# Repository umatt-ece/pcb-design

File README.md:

# pcb-design
Schematics, documentation, and guidelines for all of our custom PCB projects.

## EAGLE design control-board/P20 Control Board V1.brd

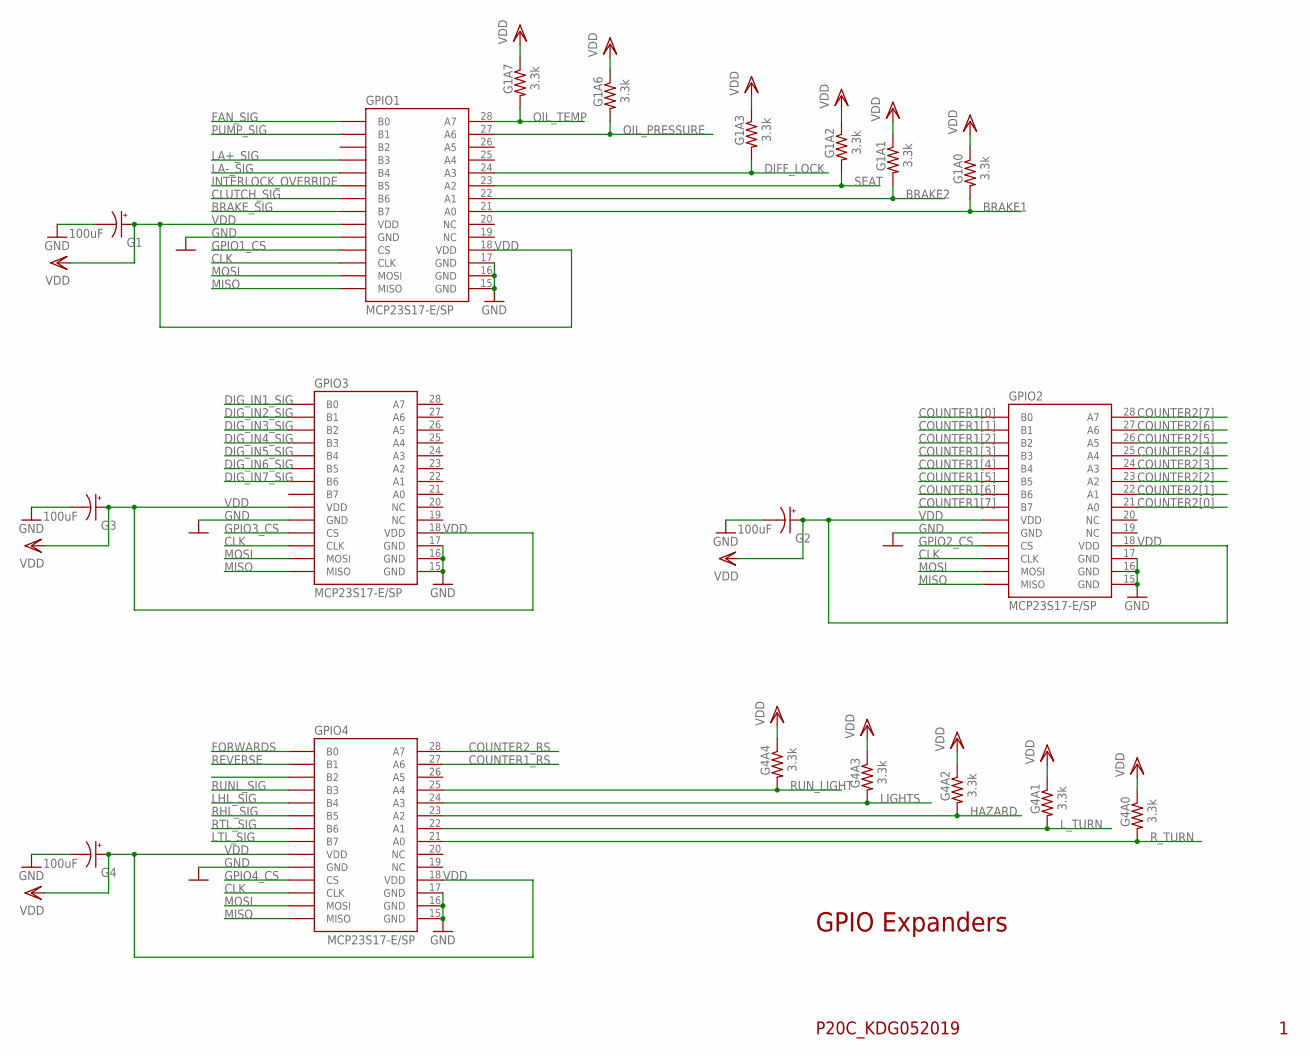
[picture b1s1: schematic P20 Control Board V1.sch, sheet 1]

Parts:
G1, G2, G3, G4: 100uF; TAP5-80
G1A0, G1A1, G1A2, G1A3, G1A6, G1A7, G4A0, G4A1, G4A2, G4A3, G4A4: 3.3k; 0207/10
GPIO1, GPIO2, GPIO3, GPIO4: MCP23S17-E/SP; GPIO_XPDR

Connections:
BRAKE1: G1A0.2, GPIO1.21 (A0); also elsewhere on the board
BRAKE2: G1A1.2, GPIO1.22 (A1); also elsewhere on the board
BRAKE_SIG: GPIO1.8 (B7); also elsewhere on the board
CLK: GPIO1.12 (CLK), GPIO2.12 (CLK), GPIO3.12 (CLK), GPIO4.12 (CLK); also elsewhere on the board
CLUTCH_SIG: GPIO1.7 (B6); also elsewhere on the board
COUNTER1[0]: GPIO2.1 (B0); also elsewhere on the board
COUNTER1[1]: GPIO2.2 (B1); also elsewhere on the board
COUNTER1[2]: GPIO2.3 (B2); also elsewhere on the board
COUNTER1[3]: GPIO2.4 (B3); also elsewhere on the board
COUNTER1[4]: GPIO2.5 (B4); also elsewhere on the board
COUNTER1[5]: GPIO2.6 (B5); also elsewhere on the board
COUNTER1[6]: GPIO2.7 (B6); also elsewhere on the board
COUNTER1[7]: GPIO2.8 (B7); also elsewhere on the board
COUNTER1_RS: GPIO4.27 (A6); also elsewhere on the board
COUNTER2[0]: GPIO2.21 (A0); also elsewhere on the board
COUNTER2[1]: GPIO2.22 (A1); also elsewhere on the board
COUNTER2[2]: GPIO2.23 (A2); also elsewhere on the board
COUNTER2[3]: GPIO2.24 (A3); also elsewhere on the board
COUNTER2[4]: GPIO2.25 (A4); also elsewhere on the board
COUNTER2[5]: GPIO2.26 (A5); also elsewhere on the board
COUNTER2[6]: GPIO2.27 (A6); also elsewhere on the board
COUNTER2[7]: GPIO2.28 (A7); also elsewhere on the board
COUNTER2_RS: GPIO4.28 (A7); also elsewhere on the board
DIFF_LOCK: G1A3.2, GPIO1.24 (A3); also elsewhere on the board
DIG_IN1_SIG: GPIO3.1 (B0); also elsewhere on the board
DIG_IN2_SIG: GPIO3.2 (B1); also elsewhere on the board
DIG_IN3_SIG: GPIO3.3 (B2); also elsewhere on the board
DIG_IN4_SIG: GPIO3.4 (B3); also elsewhere on the board
DIG_IN5_SIG: GPIO3.5 (B4); also elsewhere on the board
DIG_IN6_SIG: GPIO3.6 (B5); also elsewhere on the board
DIG_IN7_SIG: GPIO3.7 (B6); also elsewhere on the board
FAN_SIG: GPIO1.1 (B0); also elsewhere on the board
FORWARDS: GPIO4.1 (B0)
GND: G1.-, G2.-, G3.-, G4.-, GPIO1.10 (GND), GPIO1.15 (GND), GPIO1.16 (GND), GPIO1.17 (GND), GPIO2.10 (GND), GPIO2.15 (GND), GPIO2.16 (GND), GPIO2.17 (GND), GPIO3.10 (GND), GPIO3.15 (GND), GPIO3.16 (GND), GPIO3.17 (GND), GPIO4.10 (GND), GPIO4.15 (GND), GPIO4.16 (GND), GPIO4.17 (GND); also elsewhere on the board
GPIO1_CS: GPIO1.11 (CS); also elsewhere on the board
GPIO2_CS: GPIO2.11 (CS); also elsewhere on the board
GPIO3_CS: GPIO3.11 (CS); also elsewhere on the board
GPIO4_CS: GPIO4.11 (CS); also elsewhere on the board
HAZARD: G4A2.2, GPIO4.23 (A2); also elsewhere on the board
INTERLOCK_OVERRIDE: GPIO1.6 (B5); also elsewhere on the board
LA+_SIG: GPIO1.4 (B3); also elsewhere on the board
LA-_SIG: GPIO1.5 (B4); also elsewhere on the board
LHL_SIG: GPIO4.5 (B4); also elsewhere on the board
LIGHTS: G4A3.2, GPIO4.24 (A3); also elsewhere on the board
LTL_SIG: GPIO4.8 (B7); also elsewhere on the board
L_TURN: G4A1.2, GPIO4.22 (A1); also elsewhere on the board
MISO: GPIO1.14 (MISO), GPIO2.14 (MISO), GPIO3.14 (MISO), GPIO4.14 (MISO); also elsewhere on the board
MOSI: GPIO1.13 (MOSI), GPIO2.13 (MOSI), GPIO3.13 (MOSI), GPIO4.13 (MOSI); also elsewhere on the board
OIL_PRESSURE: G1A6.2, GPIO1.27 (A6); also elsewhere on the board
OIL_TEMP: G1A7.2, GPIO1.28 (A7); also elsewhere on the board
PUMP_SIG: GPIO1.2 (B1); also elsewhere on the board
REVERSE: GPIO4.2 (B1)
RHL_SIG: GPIO4.6 (B5); also elsewhere on the board
RTL_SIG: GPIO4.7 (B6); also elsewhere on the board
RUNL_SIG: GPIO4.4 (B3); also elsewhere on the board
RUN_LIGHT: G4A4.2, GPIO4.25 (A4); also elsewhere on the board
R_TURN: G4A0.2, GPIO4.21 (A0); also elsewhere on the board
SEAT: G1A2.2, GPIO1.23 (A2); also elsewhere on the board
VDD: G1.+, G1A0.1, G1A1.1, G1A2.1, G1A3.1, G1A6.1, G1A7.1, G2.+, G3.+, G4.+, G4A0.1, G4A1.1, G4A2.1, G4A3.1, G4A4.1, GPIO1.9 (VDD), GPIO1.18 (VDD), GPIO2.9 (VDD), GPIO2.18 (VDD), GPIO3.9 (VDD), GPIO3.18 (VDD), GPIO4.9 (VDD), GPIO4.18 (VDD); also elsewhere on the board

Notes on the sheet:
GPIO Expanders
P20C_KDG052019

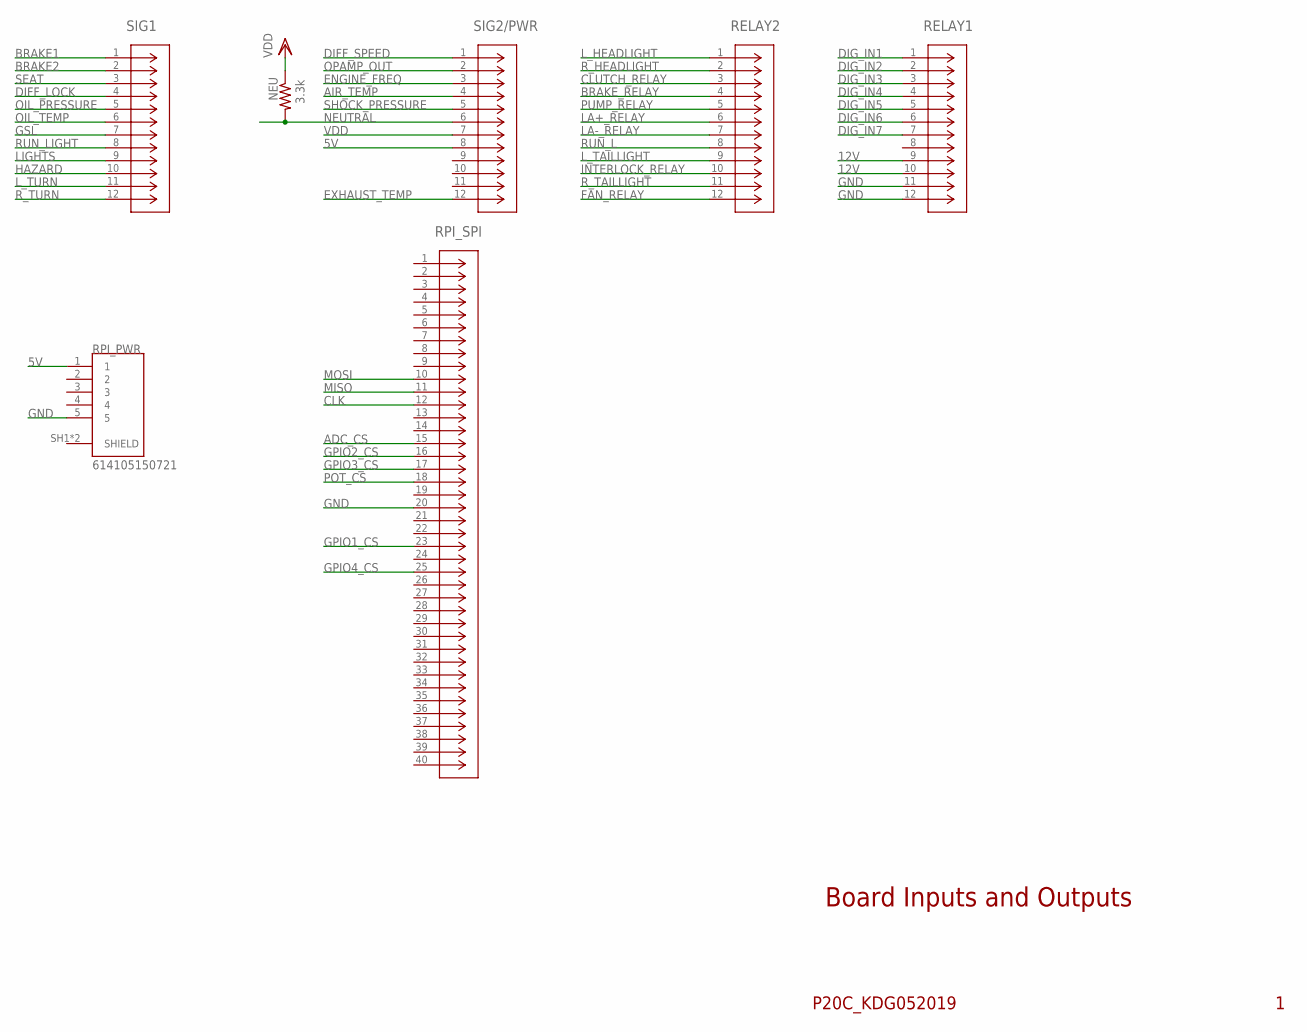
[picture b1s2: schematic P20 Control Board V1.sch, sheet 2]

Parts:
NEU: 3.3k; 0207/10
RELAY1, RELAY2: DTM13-12PA; CONN12_DTM13-12PA
RPI_PWR: 614105150721; WURTH_614105150721
RPI_SPI: 1-746610-9; CON40_P100X100-RIBBON
SIG1, SIG2/PWR: DTM13-12PA; CONN12_DTM13-12PA

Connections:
5V: RPI_PWR.1, SIG2/PWR.8; also elsewhere on the board
12V: RELAY1.9, RELAY1.10; also elsewhere on the board
ADC_CS: RPI_SPI.15; also elsewhere on the board
AIR_TEMP: SIG2/PWR.4; also elsewhere on the board
BRAKE1: SIG1.1; also elsewhere on the board
BRAKE2: SIG1.2; also elsewhere on the board
BRAKE_RELAY: RELAY2.4; also elsewhere on the board
CLK: RPI_SPI.12; also elsewhere on the board
CLUTCH_RELAY: RELAY2.3; also elsewhere on the board
DIFF_LOCK: SIG1.4; also elsewhere on the board
DIFF_SPEED: SIG2/PWR.1; also elsewhere on the board
DIG_IN1: RELAY1.1; also elsewhere on the board
DIG_IN2: RELAY1.2; also elsewhere on the board
DIG_IN3: RELAY1.3; also elsewhere on the board
DIG_IN4: RELAY1.4; also elsewhere on the board
DIG_IN5: RELAY1.5; also elsewhere on the board
DIG_IN6: RELAY1.6; also elsewhere on the board
DIG_IN7: RELAY1.7; also elsewhere on the board
ENGINE_FREQ: SIG2/PWR.3; also elsewhere on the board
EXHAUST_TEMP: SIG2/PWR.12; also elsewhere on the board
FAN_RELAY: RELAY2.12; also elsewhere on the board
GND: RELAY1.11, RELAY1.12, RPI_PWR.5, RPI_SPI.20; also elsewhere on the board
GPIO1_CS: RPI_SPI.23; also elsewhere on the board
GPIO2_CS: RPI_SPI.16; also elsewhere on the board
GPIO3_CS: RPI_SPI.17; also elsewhere on the board
GPIO4_CS: RPI_SPI.25; also elsewhere on the board
GSL: SIG1.7; also elsewhere on the board
HAZARD: SIG1.10; also elsewhere on the board
INTERLOCK_RELAY: RELAY2.10; also elsewhere on the board
LA+_RELAY: RELAY2.6; also elsewhere on the board
LA-_RELAY: RELAY2.7; also elsewhere on the board
LIGHTS: SIG1.9; also elsewhere on the board
L_HEADLIGHT: RELAY2.1; also elsewhere on the board
L_TAILLIGHT: RELAY2.9; also elsewhere on the board
L_TURN: SIG1.11; also elsewhere on the board
MISO: RPI_SPI.11; also elsewhere on the board
MOSI: RPI_SPI.10; also elsewhere on the board
NEUTRAL: NEU.2, SIG2/PWR.6; also elsewhere on the board
OIL_PRESSURE: SIG1.5; also elsewhere on the board
OIL_TEMP: SIG1.6; also elsewhere on the board
OPAMP_OUT: SIG2/PWR.2; also elsewhere on the board
POT_CS: RPI_SPI.18; also elsewhere on the board
PUMP_RELAY: RELAY2.5; also elsewhere on the board
RUN_L: RELAY2.8; also elsewhere on the board
RUN_LIGHT: SIG1.8; also elsewhere on the board
R_HEADLIGHT: RELAY2.2; also elsewhere on the board
R_TAILLIGHT: RELAY2.11; also elsewhere on the board
R_TURN: SIG1.12; also elsewhere on the board
SEAT: SIG1.3; also elsewhere on the board
SHOCK_PRESSURE: SIG2/PWR.5; also elsewhere on the board
VDD: NEU.1, SIG2/PWR.7; also elsewhere on the board

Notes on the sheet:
Board Inputs and Outputs
P20C_KDG052019

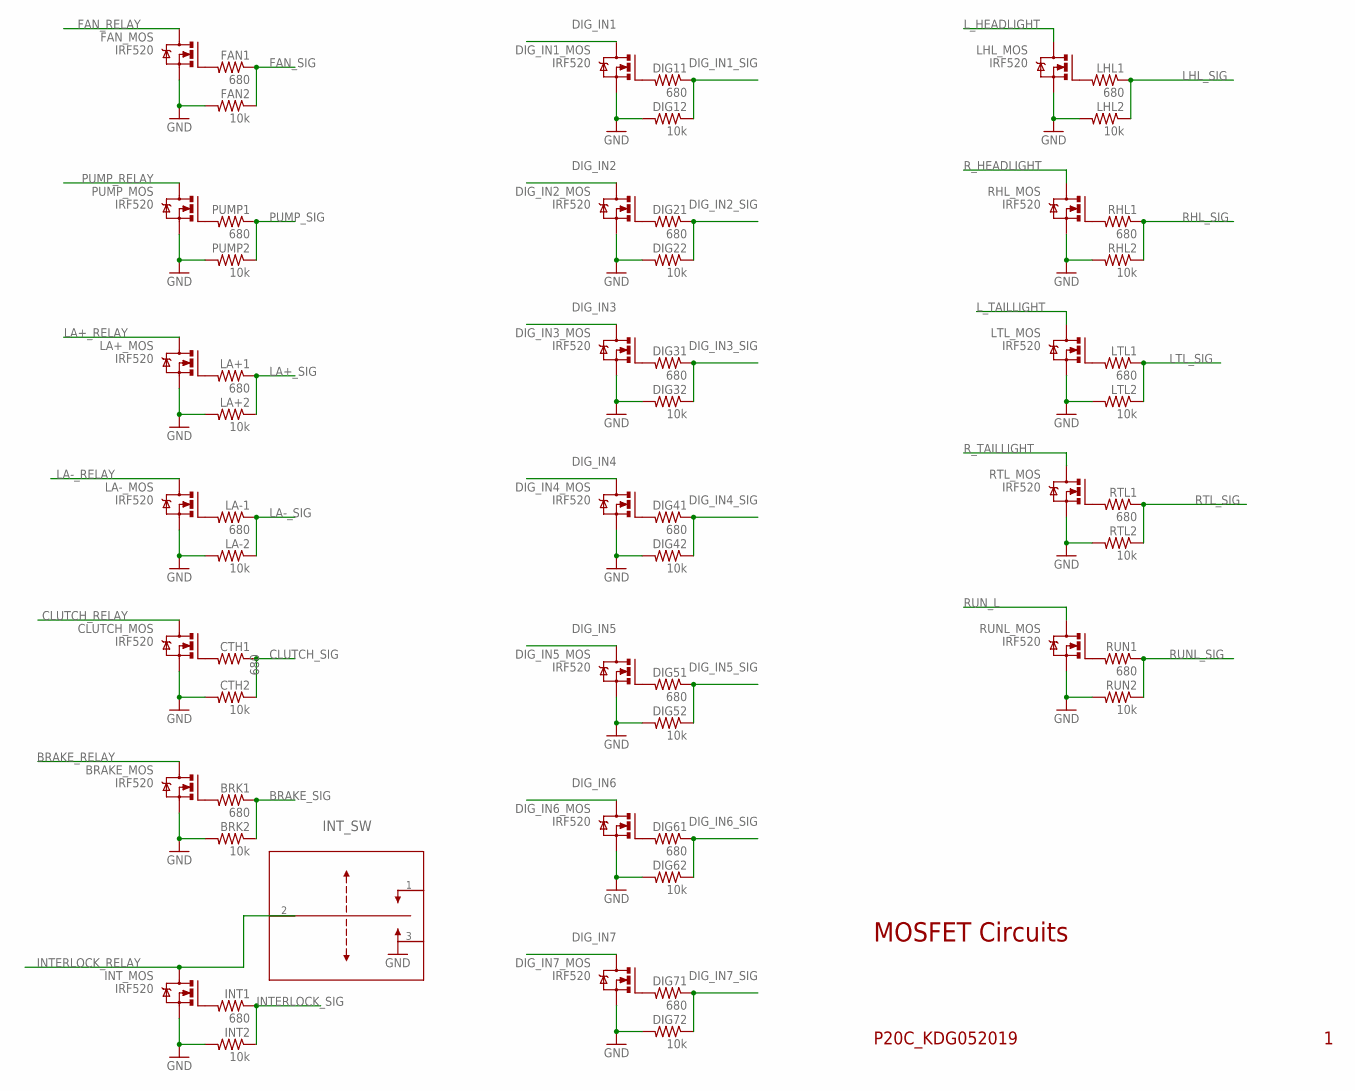
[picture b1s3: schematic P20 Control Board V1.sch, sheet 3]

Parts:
BRAKE_MOS: IRF520; TO220BV
BRK1: 680; 0207/10
BRK2: 10k; 0207/10
CLUTCH_MOS: IRF520; TO220BV
CTH1: 680; 0207/10
CTH2: 10k; 0207/10
DIG11, DIG21, DIG31, DIG41, DIG51, DIG61, DIG71: 680; 0207/10
DIG12, DIG22, DIG32, DIG42, DIG52, DIG62, DIG72: 10k; 0207/10
DIG_IN1_MOS, DIG_IN2_MOS, DIG_IN3_MOS, DIG_IN4_MOS, DIG_IN5_MOS, DIG_IN6_MOS, DIG_IN7_MOS: IRF520; TO220BV
FAN1: 680; 0207/10
FAN2: 10k; 0207/10
FAN_MOS: IRF520; TO220BV
INT1: 680; 0207/10
INT2: 10k; 0207/10
INT_MOS: IRF520; TO220BV
INT_SW: 1101M2S3CQE2
LA+1: 680; 0207/10
LA+2: 10k; 0207/10
LA+_MOS: IRF520; TO220BV
LA-1: 680; 0207/10
LA-2: 10k; 0207/10
LA-_MOS: IRF520; TO220BV
LHL1: 680; 0207/10
LHL2: 10k; 0207/10
LHL_MOS: IRF520; TO220BV
LTL1: 680; 0207/10
LTL2: 10k; 0207/10
LTL_MOS: IRF520; TO220BV
PUMP1: 680; 0207/10
PUMP2: 10k; 0207/10
PUMP_MOS: IRF520; TO220BV
RHL1: 680; 0207/10
RHL2: 10k; 0207/10
RHL_MOS: IRF520; TO220BV
RTL1: 680; 0207/10
RTL2: 10k; 0207/10
RTL_MOS: IRF520; TO220BV
RUN1: 680; 0207/10
RUN2: 10k; 0207/10
RUNL_MOS: IRF520; TO220BV

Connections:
BRAKE_RELAY: BRAKE_MOS.D; also elsewhere on the board
BRAKE_SIG: BRK1.1, BRK2.1; also elsewhere on the board
CLUTCH_RELAY: CLUTCH_MOS.D; also elsewhere on the board
CLUTCH_SIG: CTH1.1, CTH2.1; also elsewhere on the board
DIG_IN1: DIG_IN1_MOS.D; also elsewhere on the board
DIG_IN1_SIG: DIG11.1, DIG12.1; also elsewhere on the board
DIG_IN2: DIG_IN2_MOS.D; also elsewhere on the board
DIG_IN2_SIG: DIG21.1, DIG22.1; also elsewhere on the board
DIG_IN3: DIG_IN3_MOS.D; also elsewhere on the board
DIG_IN3_SIG: DIG31.1, DIG32.1; also elsewhere on the board
DIG_IN4: DIG_IN4_MOS.D; also elsewhere on the board
DIG_IN4_SIG: DIG41.1, DIG42.1; also elsewhere on the board
DIG_IN5: DIG_IN5_MOS.D; also elsewhere on the board
DIG_IN5_SIG: DIG51.1, DIG52.1; also elsewhere on the board
DIG_IN6: DIG_IN6_MOS.D; also elsewhere on the board
DIG_IN6_SIG: DIG61.1, DIG62.1; also elsewhere on the board
DIG_IN7: DIG_IN7_MOS.D; also elsewhere on the board
DIG_IN7_SIG: DIG71.1, DIG72.1; also elsewhere on the board
FAN_RELAY: FAN_MOS.D; also elsewhere on the board
FAN_SIG: FAN1.1, FAN2.1; also elsewhere on the board
GND: BRAKE_MOS.S, BRK2.2, CLUTCH_MOS.S, CTH2.2, DIG12.2, DIG22.2, DIG32.2, DIG42.2, DIG52.2, DIG62.2, DIG72.2, DIG_IN1_MOS.S, DIG_IN2_MOS.S, DIG_IN3_MOS.S, DIG_IN4_MOS.S, DIG_IN5_MOS.S, DIG_IN6_MOS.S, DIG_IN7_MOS.S, FAN2.2, FAN_MOS.S, INT2.2, INT_MOS.S, INT_SW.3, LA+2.2, LA+_MOS.S, LA-2.2, LA-_MOS.S, LHL2.2, LHL_MOS.S, LTL2.2, LTL_MOS.S, PUMP2.2, PUMP_MOS.S, RHL2.2, RHL_MOS.S, RTL2.2, RTL_MOS.S, RUN2.2, RUNL_MOS.S; also elsewhere on the board
INTERLOCK_RELAY: INT_MOS.D, INT_SW.2; also elsewhere on the board
INTERLOCK_SIG: INT1.1, INT2.1; also elsewhere on the board
LA+_RELAY: LA+_MOS.D; also elsewhere on the board
LA+_SIG: LA+1.1, LA+2.1; also elsewhere on the board
LA-_RELAY: LA-_MOS.D; also elsewhere on the board
LA-_SIG: LA-1.1, LA-2.1; also elsewhere on the board
LHL_SIG: LHL1.1, LHL2.1; also elsewhere on the board
LTL_SIG: LTL1.1, LTL2.1; also elsewhere on the board
L_HEADLIGHT: LHL_MOS.D; also elsewhere on the board
L_TAILLIGHT: LTL_MOS.D; also elsewhere on the board
unnamed: FAN1.2, FAN_MOS.G
unnamed: PUMP1.2, PUMP_MOS.G
unnamed: LA+1.2, LA+_MOS.G
unnamed: LA-1.2, LA-_MOS.G
unnamed: INT1.2, INT_MOS.G
unnamed: DIG61.2, DIG_IN6_MOS.G
unnamed: DIG71.2, DIG_IN7_MOS.G
unnamed: DIG41.2, DIG_IN4_MOS.G
unnamed: DIG51.2, DIG_IN5_MOS.G
unnamed: DIG11.2, DIG_IN1_MOS.G
unnamed: DIG21.2, DIG_IN2_MOS.G
unnamed: DIG31.2, DIG_IN3_MOS.G
unnamed: LHL1.2, LHL_MOS.G
unnamed: RHL1.2, RHL_MOS.G
unnamed: LTL1.2, LTL_MOS.G
unnamed: RTL1.2, RTL_MOS.G
unnamed: RUN1.2, RUNL_MOS.G
unnamed: CLUTCH_MOS.G, CTH1.2
unnamed: BRAKE_MOS.G, BRK1.2
PUMP_RELAY: PUMP_MOS.D; also elsewhere on the board
PUMP_SIG: PUMP1.1, PUMP2.1; also elsewhere on the board
RHL_SIG: RHL1.1, RHL2.1; also elsewhere on the board
RTL_SIG: RTL1.1, RTL2.1; also elsewhere on the board
RUNL_SIG: RUN1.1, RUN2.1; also elsewhere on the board
RUN_L: RUNL_MOS.D; also elsewhere on the board
R_HEADLIGHT: RHL_MOS.D; also elsewhere on the board
R_TAILLIGHT: RTL_MOS.D; also elsewhere on the board

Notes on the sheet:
MOSFET Circuits
P20C_KDG052019

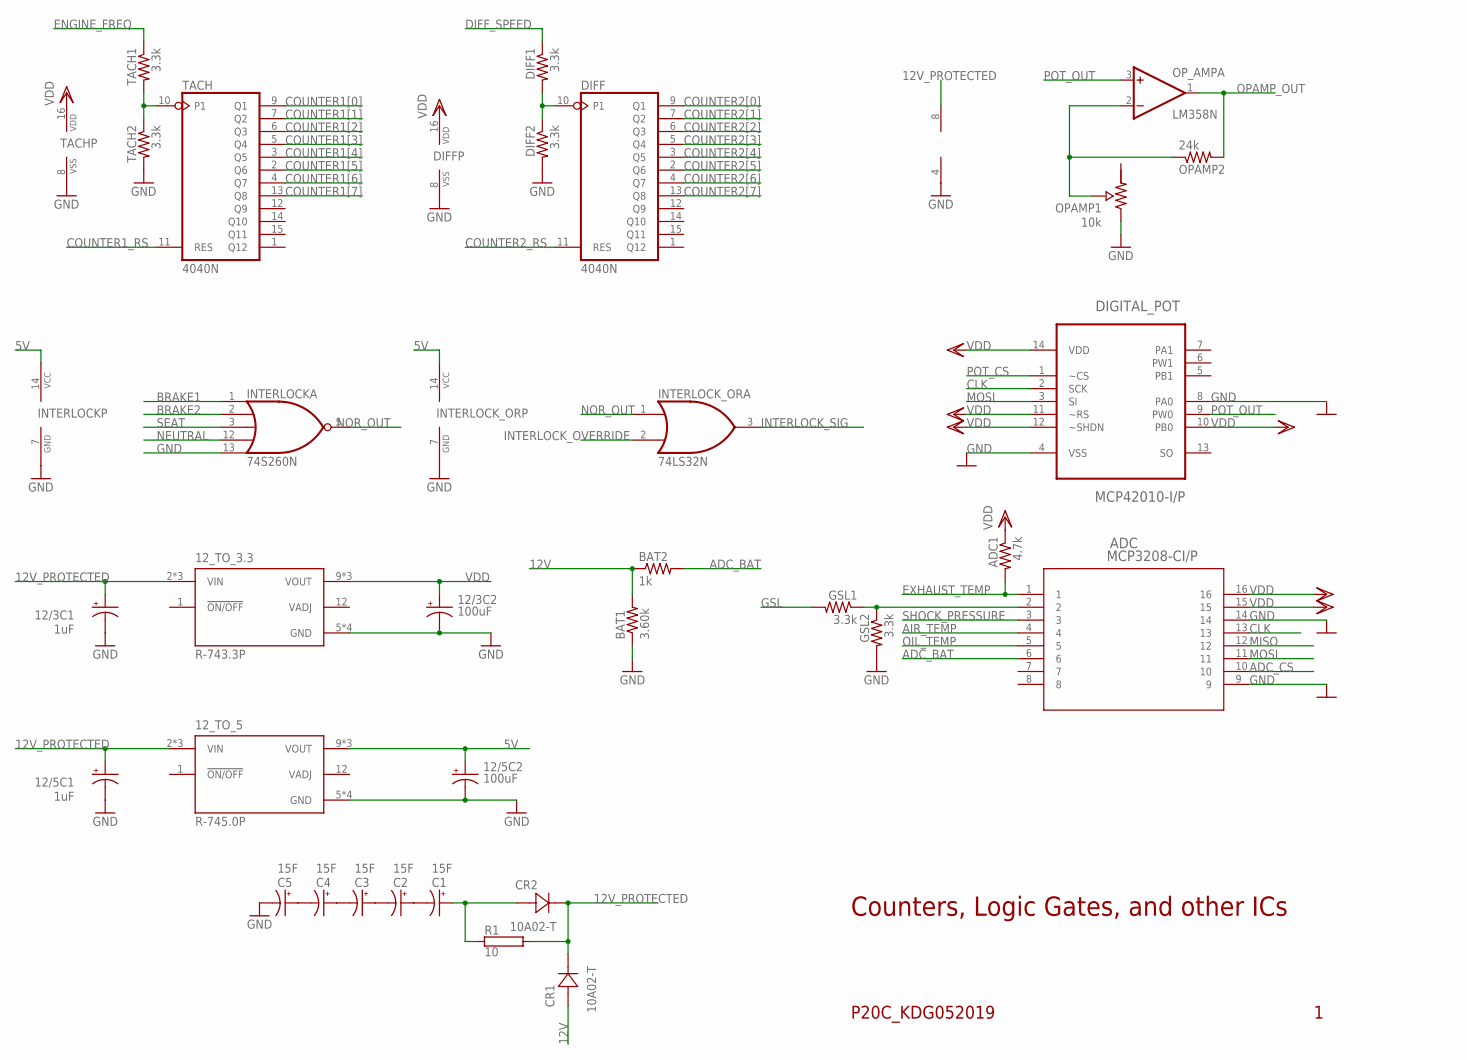
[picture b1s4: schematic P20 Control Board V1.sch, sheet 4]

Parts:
12/3C1, 12/5C1: 1uF; TAP5-80
12/3C2, 12/5C2: 100uF; TAP5-80
12_TO_3.3: R-743.3P; CONV_R-743.3P
12_TO_5: R-745.0P; CONV_R-745.0P
ADC: MCP3208-CI/P; PDIP16_300MC
ADC1: 4.7k; 0207/10
BAT1: 3.60k; 0207/10
BAT2: 1k; 0207/10
C1, C2, C3, C4, C5: 15F; B45181D
CR1, CR2: 10A02-T; R-6
DIFF: 4040N; DIL16
DIFF1, DIFF2: 3.3k; 0207/10
DIGITAL_POT: MCP42010-I/P; DIP254P762X432-14
GSL1, GSL2: 3.3k; 0207/10
INTERLOCK: 74S260N; DIL14
INTERLOCK_OR: 74LS32N; DIL14
OPAMP1: 10k; POT_3386F
OPAMP2: 24k; 0207/10
OP_AMP: LM358N; DIL08
R1: 10; TO-247-2V
TACH: 4040N; DIL16
TACH1, TACH2: 3.3k; 0207/10

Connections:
5V: 12/5C2.+, 12_TO_5.9 (VOUT), 12_TO_5.10 (VOUT), 12_TO_5.11 (VOUT), INTERLOCK.14 (VCC), INTERLOCK_OR.14 (VCC); also elsewhere on the board
12V: BAT1.2, BAT2.1, CR1.2; also elsewhere on the board
12V_PROTECTED: 12/3C1.+, 12/5C1.+, 12_TO_3.3.2 (VIN), 12_TO_3.3.3 (VIN), 12_TO_3.3.4 (VIN), 12_TO_5.2 (VIN), 12_TO_5.3 (VIN), 12_TO_5.4 (VIN), CR1.1, CR2.1, OP_AMP.8 (V+), R1.2
ADC_BAT: ADC.6, BAT2.2
ADC_CS: ADC.10; also elsewhere on the board
AIR_TEMP: ADC.4; also elsewhere on the board
BRAKE1: INTERLOCK.1 (I0); also elsewhere on the board
BRAKE2: INTERLOCK.2 (I1); also elsewhere on the board
CLK: ADC.13, DIGITAL_POT.2 (SCK); also elsewhere on the board
COUNTER1[0]: TACH.9 (Q1); also elsewhere on the board
COUNTER1[1]: TACH.7 (Q2); also elsewhere on the board
COUNTER1[2]: TACH.6 (Q3); also elsewhere on the board
COUNTER1[3]: TACH.5 (Q4); also elsewhere on the board
COUNTER1[4]: TACH.3 (Q5); also elsewhere on the board
COUNTER1[5]: TACH.2 (Q6); also elsewhere on the board
COUNTER1[6]: TACH.4 (Q7); also elsewhere on the board
COUNTER1[7]: TACH.13 (Q8); also elsewhere on the board
COUNTER1_RS: TACH.11 (RES); also elsewhere on the board
COUNTER2[0]: DIFF.9 (Q1); also elsewhere on the board
COUNTER2[1]: DIFF.7 (Q2); also elsewhere on the board
COUNTER2[2]: DIFF.6 (Q3); also elsewhere on the board
COUNTER2[3]: DIFF.5 (Q4); also elsewhere on the board
COUNTER2[4]: DIFF.3 (Q5); also elsewhere on the board
COUNTER2[5]: DIFF.2 (Q6); also elsewhere on the board
COUNTER2[6]: DIFF.4 (Q7); also elsewhere on the board
COUNTER2[7]: DIFF.13 (Q8); also elsewhere on the board
COUNTER2_RS: DIFF.11 (RES); also elsewhere on the board
DIFF_SPEED: DIFF1.1; also elsewhere on the board
ENGINE_FREQ: TACH1.1; also elsewhere on the board
EXHAUST_TEMP: ADC.1, ADC1.2; also elsewhere on the board
GND: 12/3C1.-, 12/3C2.-, 12/5C1.-, 12/5C2.-, 12_TO_3.3.5 (GND), 12_TO_3.3.6 (GND), 12_TO_3.3.7 (GND), 12_TO_3.3.8 (GND), 12_TO_5.5 (GND), 12_TO_5.6 (GND), 12_TO_5.7 (GND), 12_TO_5.8 (GND), ADC.9, ADC.14, BAT1.1, C5.-, DIFF.8 (VSS), DIFF2.2, DIGITAL_POT.4 (VSS), DIGITAL_POT.8 (PA0), GSL2.2, INTERLOCK.7 (GND), INTERLOCK.13 (I4), INTERLOCK_OR.7 (GND), OPAMP1.1, OP_AMP.4 (V-), TACH.8 (VSS), TACH2.2; also elsewhere on the board
GSL: GSL1.2; also elsewhere on the board
INTERLOCK_OVERRIDE: INTERLOCK_OR.2 (I1); also elsewhere on the board
INTERLOCK_SIG: INTERLOCK_OR.3 (O); also elsewhere on the board
MISO: ADC.12; also elsewhere on the board
MOSI: ADC.11, DIGITAL_POT.3 (SI); also elsewhere on the board
unnamed: OPAMP1.2, OPAMP2.1, OP_AMP.2 (-IN)
unnamed: ADC.2, GSL1.1, GSL2.1
unnamed: TACH.10 (P1), TACH1.2, TACH2.1
unnamed: DIFF.10 (P1), DIFF1.2, DIFF2.1
unnamed: C1.-, C2.+
unnamed: C1.+, CR2.2, R1.1
unnamed: C2.-, C3.+
unnamed: C3.-, C4.+
unnamed: C4.-, C5.+
NEUTRAL: INTERLOCK.12 (I3); also elsewhere on the board
NOR_OUT: INTERLOCK.5 (O), INTERLOCK_OR.1 (I0)
OIL_TEMP: ADC.5; also elsewhere on the board
OPAMP_OUT: OPAMP2.2, OP_AMP.1 (OUT); also elsewhere on the board
POT_CS: DIGITAL_POT.1 (~CS); also elsewhere on the board
POT_OUT: DIGITAL_POT.9 (PW0), OP_AMP.3 (+IN)
SEAT: INTERLOCK.3 (I2); also elsewhere on the board
SHOCK_PRESSURE: ADC.3; also elsewhere on the board
VDD: 12/3C2.+, 12_TO_3.3.9 (VOUT), 12_TO_3.3.10 (VOUT), 12_TO_3.3.11 (VOUT), ADC.15, ADC.16, ADC1.1, DIFF.16 (VDD), DIGITAL_POT.10 (PB0), DIGITAL_POT.11 (~RS), DIGITAL_POT.12 (~SHDN), DIGITAL_POT.14 (VDD), TACH.16 (VDD); also elsewhere on the board

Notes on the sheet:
Counters, Logic Gates, and other ICs
P20C_KDG052019

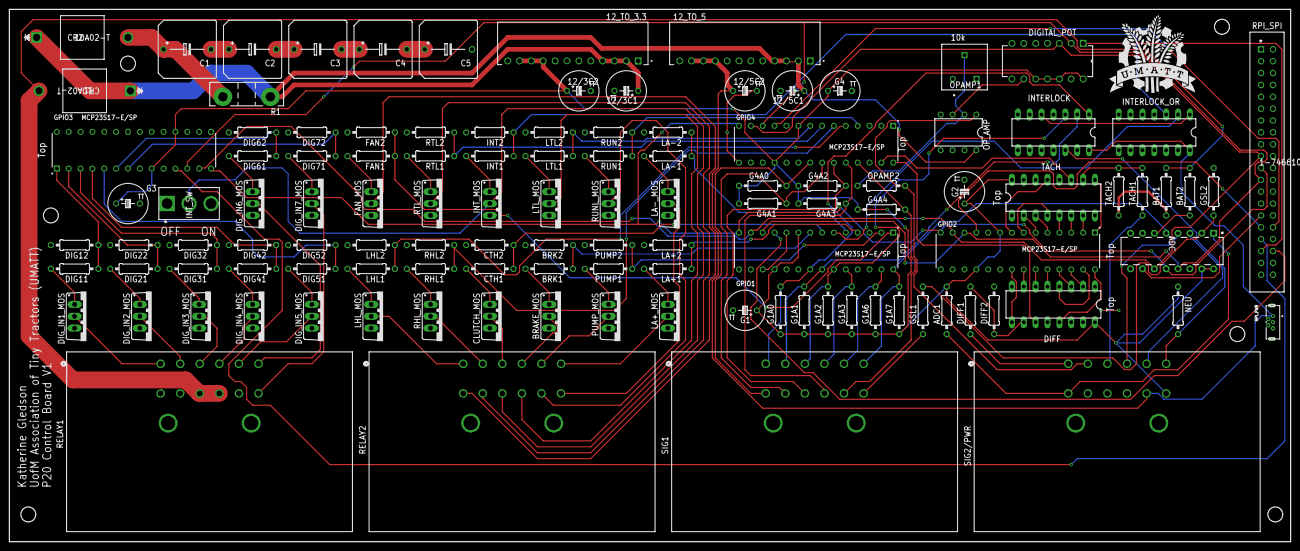
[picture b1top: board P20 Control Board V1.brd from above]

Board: 2 copper layers, 274.3 x 114.0 mm, 116 parts (0 on the bottom side), 121 nets.

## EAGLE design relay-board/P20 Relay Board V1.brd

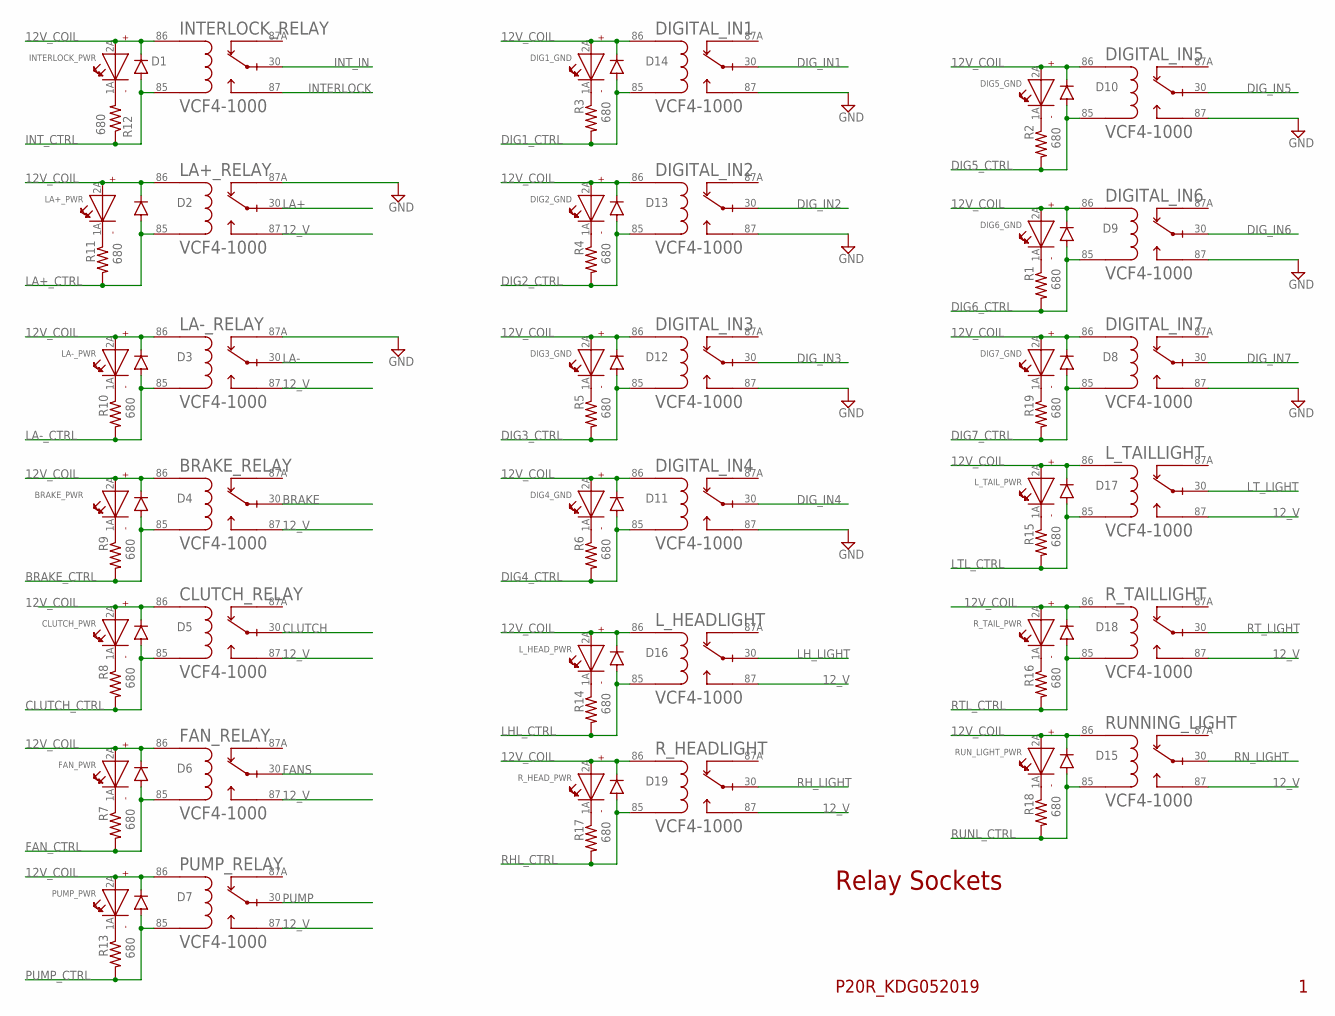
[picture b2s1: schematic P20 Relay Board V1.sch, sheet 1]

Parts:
BRAKE_PWR: WL-TMRW151033BS03000-B; LED-3MM-ROUND
BRAKE_RELAY: VCF4-1000; TE_VCF4-1000
CLUTCH_PWR: WL-TMRW151033BS03000-B; LED-3MM-ROUND
CLUTCH_RELAY: VCF4-1000; TE_VCF4-1000
D1, D2, D3, D4, D5, D6, D7, D8, D9, D10, D11, D12, D13, D14, D15, D16, D17, D18, D19: 1N4004; DO41-10
DIG1_GND, DIG2_GND, DIG3_GND, DIG4_GND, DIG5_GND, DIG6_GND, DIG7_GND: WL-TMRW151033BS03000-B; LED-3MM-ROUND
DIGITAL_IN1, DIGITAL_IN2, DIGITAL_IN3, DIGITAL_IN4, DIGITAL_IN5, DIGITAL_IN6, DIGITAL_IN7: VCF4-1000; TE_VCF4-1000
FAN_PWR: WL-TMRW151033BS03000-B; LED-3MM-ROUND
FAN_RELAY: VCF4-1000; TE_VCF4-1000
INTERLOCK_PWR: WL-TMRW151033BS03000-B; LED-3MM-ROUND
INTERLOCK_RELAY: VCF4-1000; TE_VCF4-1000
LA+_PWR: WL-TMRW151033BS03000-B; LED-3MM-ROUND
LA+_RELAY: VCF4-1000; TE_VCF4-1000
LA-_PWR: WL-TMRW151033BS03000-B; LED-3MM-ROUND
LA-_RELAY: VCF4-1000; TE_VCF4-1000
L_HEADLIGHT: VCF4-1000; TE_VCF4-1000
L_HEAD_PWR: WL-TMRW151033BS03000-B; LED-3MM-ROUND
L_TAILLIGHT: VCF4-1000; TE_VCF4-1000
L_TAIL_PWR: WL-TMRW151033BS03000-B; LED-3MM-ROUND
PUMP_PWR: WL-TMRW151033BS03000-B; LED-3MM-ROUND
PUMP_RELAY: VCF4-1000; TE_VCF4-1000
R1, R2, R3, R4, R5, R6, R7, R8, R9, R10, R11, R12, R13, R14, R15, R16, R17, R18, R19: 680; 0207/10
RUNNING_LIGHT: VCF4-1000; TE_VCF4-1000
RUN_LIGHT_PWR: WL-TMRW151033BS03000-B; LED-3MM-ROUND
R_HEADLIGHT: VCF4-1000; TE_VCF4-1000
R_HEAD_PWR: WL-TMRW151033BS03000-B; LED-3MM-ROUND
R_TAILLIGHT: VCF4-1000; TE_VCF4-1000
R_TAIL_PWR: WL-TMRW151033BS03000-B; LED-3MM-ROUND

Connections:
12V_COIL: BRAKE_PWR.2A (+), BRAKE_RELAY.86, CLUTCH_PWR.2A (+), CLUTCH_RELAY.86, D1.C, D2.C, D3.C, D4.C, D5.C, D6.C, D7.C, D8.C, D9.C, D10.C, D11.C, D12.C, D13.C, D14.C, D15.C, D16.C, D17.C, D18.C, D19.C, DIG1_GND.2A (+), DIG2_GND.2A (+), DIG3_GND.2A (+), DIG4_GND.2A (+), DIG5_GND.2A (+), DIG6_GND.2A (+), DIG7_GND.2A (+), DIGITAL_IN1.86, DIGITAL_IN2.86, DIGITAL_IN3.86, DIGITAL_IN4.86, DIGITAL_IN5.86, DIGITAL_IN6.86, DIGITAL_IN7.86, FAN_PWR.2A (+), FAN_RELAY.86, INTERLOCK_PWR.2A (+), INTERLOCK_RELAY.86, LA+_PWR.2A (+), LA+_RELAY.86, LA-_PWR.2A (+), LA-_RELAY.86, L_HEADLIGHT.86, L_HEAD_PWR.2A (+), L_TAILLIGHT.86, L_TAIL_PWR.2A (+), PUMP_PWR.2A (+), PUMP_RELAY.86, RUNNING_LIGHT.86, RUN_LIGHT_PWR.2A (+), R_HEADLIGHT.86, R_HEAD_PWR.2A (+), R_TAILLIGHT.86, R_TAIL_PWR.2A (+); also elsewhere on the board
12_V: BRAKE_RELAY.87, CLUTCH_RELAY.87, FAN_RELAY.87, LA+_RELAY.87, LA-_RELAY.87, L_HEADLIGHT.87, L_TAILLIGHT.87, PUMP_RELAY.87, RUNNING_LIGHT.87, R_HEADLIGHT.87, R_TAILLIGHT.87; also elsewhere on the board
BRAKE: BRAKE_RELAY.30; also elsewhere on the board
BRAKE_CTRL: BRAKE_RELAY.85, D4.A, R9.2; also elsewhere on the board
CLUTCH: CLUTCH_RELAY.30; also elsewhere on the board
CLUTCH_CTRL: CLUTCH_RELAY.85, D5.A, R8.2; also elsewhere on the board
DIG1_CTRL: D14.A, DIGITAL_IN1.85, R3.2; also elsewhere on the board
DIG2_CTRL: D13.A, DIGITAL_IN2.85, R4.2; also elsewhere on the board
DIG3_CTRL: D12.A, DIGITAL_IN3.85, R5.2; also elsewhere on the board
DIG4_CTRL: D11.A, DIGITAL_IN4.85, R6.2; also elsewhere on the board
DIG5_CTRL: D10.A, DIGITAL_IN5.85, R2.2; also elsewhere on the board
DIG6_CTRL: D9.A, DIGITAL_IN6.85, R1.2; also elsewhere on the board
DIG7_CTRL: D8.A, DIGITAL_IN7.85, R19.2; also elsewhere on the board
DIG_IN1: DIGITAL_IN1.30; also elsewhere on the board
DIG_IN2: DIGITAL_IN2.30; also elsewhere on the board
DIG_IN3: DIGITAL_IN3.30; also elsewhere on the board
DIG_IN4: DIGITAL_IN4.30; also elsewhere on the board
DIG_IN5: DIGITAL_IN5.30; also elsewhere on the board
DIG_IN6: DIGITAL_IN6.30; also elsewhere on the board
DIG_IN7: DIGITAL_IN7.30; also elsewhere on the board
FANS: FAN_RELAY.30; also elsewhere on the board
FAN_CTRL: D6.A, FAN_RELAY.85, R7.2; also elsewhere on the board
GND: DIGITAL_IN1.87, DIGITAL_IN2.87, DIGITAL_IN3.87, DIGITAL_IN4.87, DIGITAL_IN5.87, DIGITAL_IN6.87, DIGITAL_IN7.87, LA+_RELAY.87A, LA-_RELAY.87A; also elsewhere on the board
INTERLOCK: INTERLOCK_RELAY.87; also elsewhere on the board
INT_CTRL: D1.A, INTERLOCK_RELAY.85, R12.1; also elsewhere on the board
INT_IN: INTERLOCK_RELAY.30; also elsewhere on the board
LA+: LA+_RELAY.30; also elsewhere on the board
LA+_CTRL: D2.A, LA+_RELAY.85, R11.2; also elsewhere on the board
LA-: LA-_RELAY.30; also elsewhere on the board
LA-_CTRL: D3.A, LA-_RELAY.85, R10.2; also elsewhere on the board
LHL_CTRL: D16.A, L_HEADLIGHT.85, R14.2; also elsewhere on the board
LH_LIGHT: L_HEADLIGHT.30; also elsewhere on the board
LTL_CTRL: D17.A, L_TAILLIGHT.85, R15.2; also elsewhere on the board
LT_LIGHT: L_TAILLIGHT.30; also elsewhere on the board
unnamed: DIG7_GND.1A (-), R19.1
unnamed: DIG5_GND.1A (-), R2.1
unnamed: DIG1_GND.1A (-), R3.1
unnamed: DIG2_GND.1A (-), R4.1
unnamed: DIG3_GND.1A (-), R5.1
unnamed: DIG4_GND.1A (-), R6.1
unnamed: FAN_PWR.1A (-), R7.1
unnamed: CLUTCH_PWR.1A (-), R8.1
unnamed: BRAKE_PWR.1A (-), R9.1
unnamed: LA-_PWR.1A (-), R10.1
unnamed: LA+_PWR.1A (-), R11.1
unnamed: INTERLOCK_PWR.1A (-), R12.2
unnamed: PUMP_PWR.1A (-), R13.1
unnamed: L_HEAD_PWR.1A (-), R14.1
unnamed: L_TAIL_PWR.1A (-), R15.1
unnamed: R17.1, R_HEAD_PWR.1A (-)
unnamed: R16.1, R_TAIL_PWR.1A (-)
unnamed: R18.1, RUN_LIGHT_PWR.1A (-)
unnamed: DIG6_GND.1A (-), R1.1
PUMP: PUMP_RELAY.30; also elsewhere on the board
PUMP_CTRL: D7.A, PUMP_RELAY.85, R13.2; also elsewhere on the board
RHL_CTRL: D19.A, R17.2, R_HEADLIGHT.85; also elsewhere on the board
RH_LIGHT: R_HEADLIGHT.30; also elsewhere on the board
RN_LIGHT: RUNNING_LIGHT.30; also elsewhere on the board
RTL_CTRL: D18.A, R16.2, R_TAILLIGHT.85; also elsewhere on the board
RT_LIGHT: R_TAILLIGHT.30; also elsewhere on the board
RUNL_CTRL: D15.A, R18.2, RUNNING_LIGHT.85; also elsewhere on the board

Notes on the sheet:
Relay Sockets
P20R_KDG052019
